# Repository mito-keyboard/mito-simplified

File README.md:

# Mito PCB

The pcb for my [custom keyboard](https://github.com/KOEGlike/mito)

## Sponsor

Much thanks to pcbway for sponsoring this project, the video is in the making, stay tuned! The PCBs and stencil are very high quality!!

## Gallery

## Name

Inspired by the mitosis of cells

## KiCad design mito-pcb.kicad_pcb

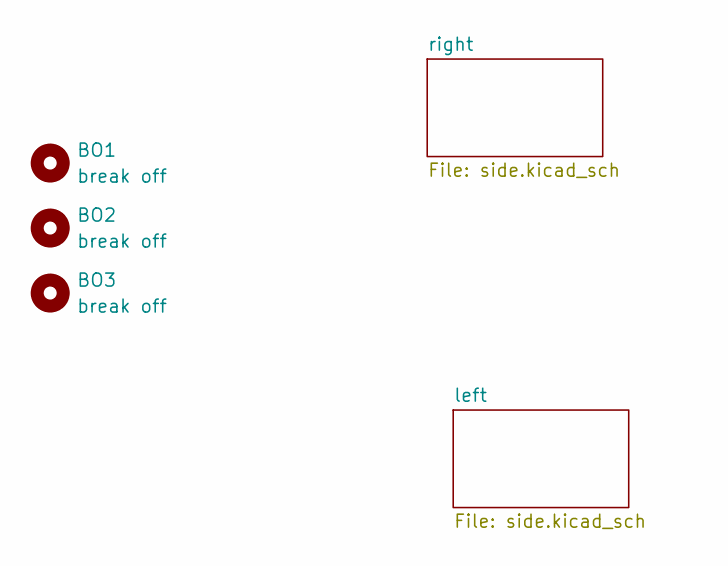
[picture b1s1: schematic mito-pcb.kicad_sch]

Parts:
BO1, BO2, BO3: break off; mouse-bite-2mm-slot

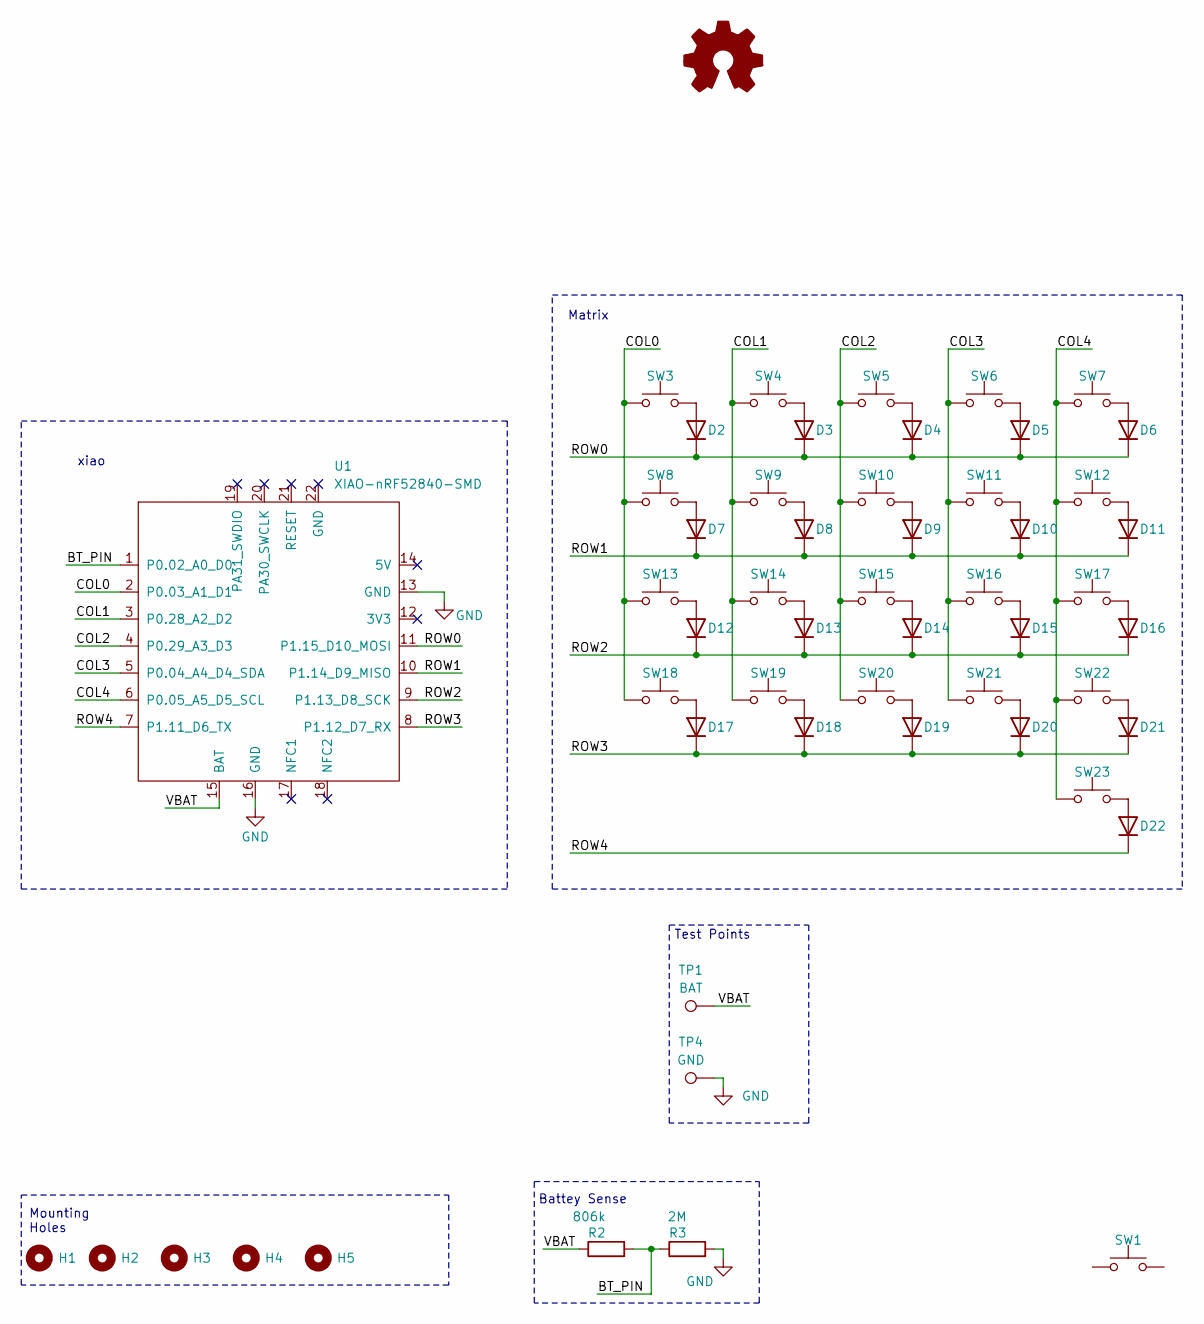
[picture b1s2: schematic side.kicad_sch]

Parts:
D2, D3, D4, D5, D6, D7, D8, D9, D10, D11, D12, D13, D14, D15, D16, D17, D18, D19, D20, D21, D22: 1N5819; D_SOD-123; LCSC C963381
H1, H2, H3, H4, H5: MountingHole; MountingHole_2mm
LOGO1: Logo_Open_Hardware_Small; BM logo
R2: 806k; R_0805_2012Metric; LCSC C3016043
R3: 2M; R_0805_2012Metric; LCSC C11512
SW1, SW3, SW4, SW5, SW6, SW7, SW8, SW9, SW10, SW11, SW12, SW13, SW14, SW15, SW16, SW17, SW18, SW19, SW20, SW21, SW22, SW23: SW_Push; SW_choc_v1_HS_CPG135001S30_1u; LCSC C5333465
TP1: BAT; TestPoint_Pad_D2.0mm
TP4: GND; TestPoint_Pad_D2.0mm
U1: XIAO-nRF52840-SMD; modified-XIAO-nRF52840-SMD

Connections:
/left/BT_PIN: R2.2, R3.1, U1.1 (P0.02_A0_D0)
/left/COL0: SW3.1, SW8.1, SW13.1, SW18.1, U1.2 (P0.03_A1_D1)
/left/COL1: SW4.1, SW9.1, SW14.1, SW19.1, U1.3 (P0.28_A2_D2)
/left/COL2: SW5.1, SW10.1, SW15.1, SW20.1, U1.4 (P0.29_A3_D3)
/left/COL3: SW6.1, SW11.1, SW16.1, SW21.1, U1.5 (P0.04_A4_D4_SDA)
/left/COL4: SW7.1, SW12.1, SW17.1, SW22.1, SW23.1, U1.6 (P0.05_A5_D5_SCL)
/left/ROW0: D2.1 (K), D3.1 (K), D4.1 (K), D5.1 (K), D6.1 (K), U1.11 (P1.15_D10_MOSI)
/left/ROW1: D7.1 (K), D8.1 (K), D9.1 (K), D10.1 (K), D11.1 (K), U1.10 (P1.14_D9_MISO)
/left/ROW2: D12.1 (K), D13.1 (K), D14.1 (K), D15.1 (K), D16.1 (K), U1.9 (P1.13_D8_SCK)
/left/ROW3: D17.1 (K), D18.1 (K), D19.1 (K), D20.1 (K), D21.1 (K), U1.8 (P1.12_D7_RX)
/left/ROW4: D22.1 (K), U1.7 (P1.11_D6_TX)
/left/VBAT: R2.1, TP1.1, U1.15 (BAT)
GND: R3.2, TP4.1, U1.13 (GND), U1.16 (GND); also elsewhere on the board
unnamed: D2.2 (A), SW3.2
unnamed: D3.2 (A), SW4.2
unnamed: D4.2 (A), SW5.2
unnamed: D5.2 (A), SW6.2
unnamed: D6.2 (A), SW7.2
unnamed: D7.2 (A), SW8.2
unnamed: D8.2 (A), SW9.2
unnamed: D9.2 (A), SW10.2
unnamed: D10.2 (A), SW11.2
unnamed: D11.2 (A), SW12.2
unnamed: D12.2 (A), SW13.2
unnamed: D13.2 (A), SW14.2
unnamed: D14.2 (A), SW15.2
unnamed: D15.2 (A), SW16.2
unnamed: D16.2 (A), SW17.2
unnamed: D17.2 (A), SW18.2
unnamed: D18.2 (A), SW19.2
unnamed: D19.2 (A), SW20.2
unnamed: D20.2 (A), SW21.2
unnamed: D21.2 (A), SW22.2
unnamed: D22.2 (A), SW23.2

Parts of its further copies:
D44, D45, D46, D47, D48, D49, D50, D51, D52, D53, D54, D55, D56, D57, D58, D59, D60, D61, D62, D63, D64: 1N5819; D_SOD-123; LCSC C963381
H6, H7, H8, H9, H10: MountingHole; MountingHole_2mm
R9: 806k; R_0805_2012Metric; LCSC C3016043
R10: 2M; R_0805_2012Metric; LCSC C11512
SW26, SW27, SW28, SW29, SW30, SW31, SW32, SW33, SW34, SW35, SW36, SW37, SW38, SW39, SW40, SW41, SW42, SW43, SW44, SW45, SW46: SW_Push; SW_choc_v1_HS_CPG135001S30_1u; LCSC C5333465
TP2: BAT; TestPoint_Pad_D2.0mm
TP8: GND; TestPoint_Pad_D2.0mm
U3: XIAO-nRF52840-SMD; modified-XIAO-nRF52840-SMD

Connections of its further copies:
/right/BT_PIN: R9.2, R10.1, U3.1 (P0.02_A0_D0)
/right/COL0: SW26.1, SW31.1, SW36.1, SW41.1, U3.2 (P0.03_A1_D1)
/right/COL1: SW27.1, SW32.1, SW37.1, SW42.1, U3.3 (P0.28_A2_D2)
/right/COL2: SW28.1, SW33.1, SW38.1, SW43.1, U3.4 (P0.29_A3_D3)
/right/COL3: SW29.1, SW34.1, SW39.1, SW44.1, U3.5 (P0.04_A4_D4_SDA)
/right/COL4: SW30.1, SW35.1, SW40.1, SW45.1, SW46.1, U3.6 (P0.05_A5_D5_SCL)
/right/ROW0: D44.1 (K), D45.1 (K), D46.1 (K), D47.1 (K), D48.1 (K), U3.11 (P1.15_D10_MOSI)
/right/ROW1: D49.1 (K), D50.1 (K), D51.1 (K), D52.1 (K), D53.1 (K), U3.10 (P1.14_D9_MISO)
/right/ROW2: D54.1 (K), D55.1 (K), D56.1 (K), D57.1 (K), D58.1 (K), U3.9 (P1.13_D8_SCK)
/right/ROW3: D59.1 (K), D60.1 (K), D61.1 (K), D62.1 (K), D63.1 (K), U3.8 (P1.12_D7_RX)
/right/ROW4: D64.1 (K), U3.7 (P1.11_D6_TX)
/right/VBAT: R9.1, TP2.1, U3.15 (BAT)
GND: R10.2, TP8.1, U3.13 (GND), U3.16 (GND); also elsewhere on the board
unnamed: D44.2 (A), SW26.2
unnamed: D45.2 (A), SW27.2
unnamed: D46.2 (A), SW28.2
unnamed: D47.2 (A), SW29.2
unnamed: D48.2 (A), SW30.2
unnamed: D49.2 (A), SW31.2
unnamed: D50.2 (A), SW32.2
unnamed: D51.2 (A), SW33.2
unnamed: D52.2 (A), SW34.2
unnamed: D53.2 (A), SW35.2
unnamed: D54.2 (A), SW36.2
unnamed: D55.2 (A), SW37.2
unnamed: D56.2 (A), SW38.2
unnamed: D57.2 (A), SW39.2
unnamed: D58.2 (A), SW40.2
unnamed: D59.2 (A), SW41.2
unnamed: D60.2 (A), SW42.2
unnamed: D61.2 (A), SW43.2
unnamed: D62.2 (A), SW44.2
unnamed: D63.2 (A), SW45.2
unnamed: D64.2 (A), SW46.2

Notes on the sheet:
Battey Sense
Matrix
Mounting Holes
Test Points
xiao

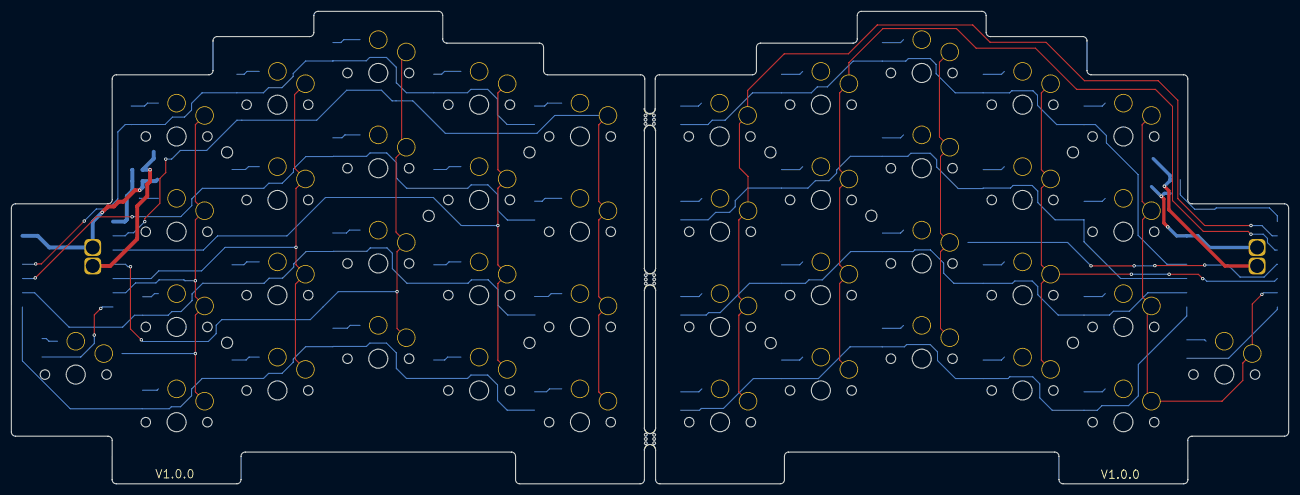
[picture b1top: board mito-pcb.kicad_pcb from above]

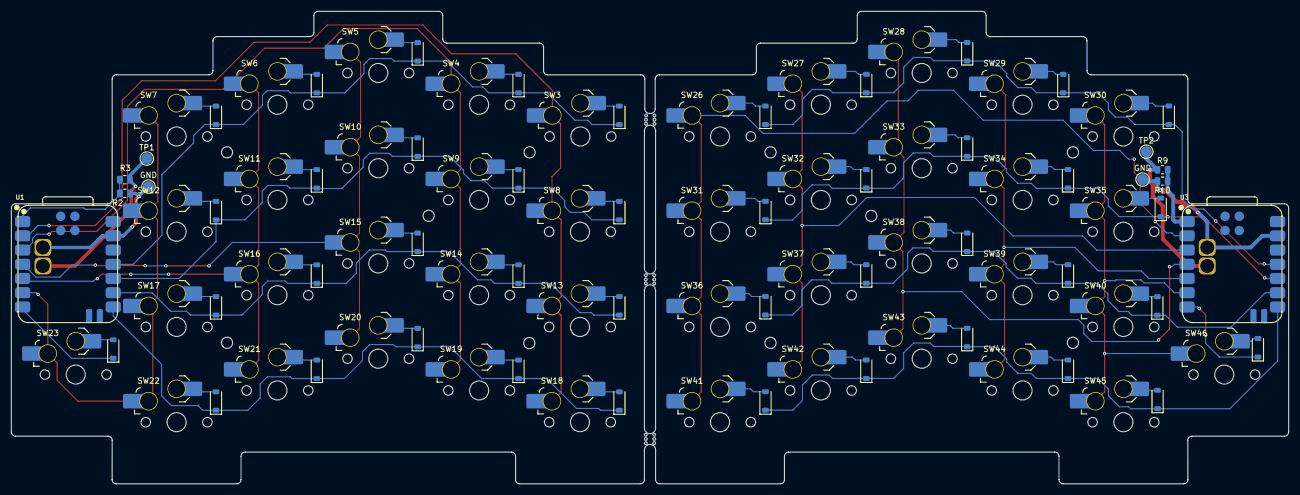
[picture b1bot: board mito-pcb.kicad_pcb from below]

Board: 2 copper layers, 228.0 x 84.3 mm, 107 parts (99 on the bottom side), 67 nets.

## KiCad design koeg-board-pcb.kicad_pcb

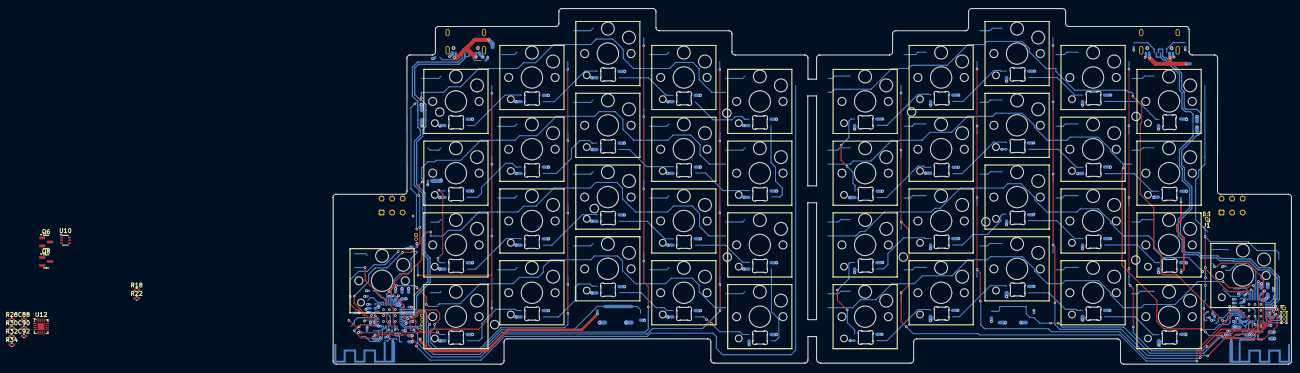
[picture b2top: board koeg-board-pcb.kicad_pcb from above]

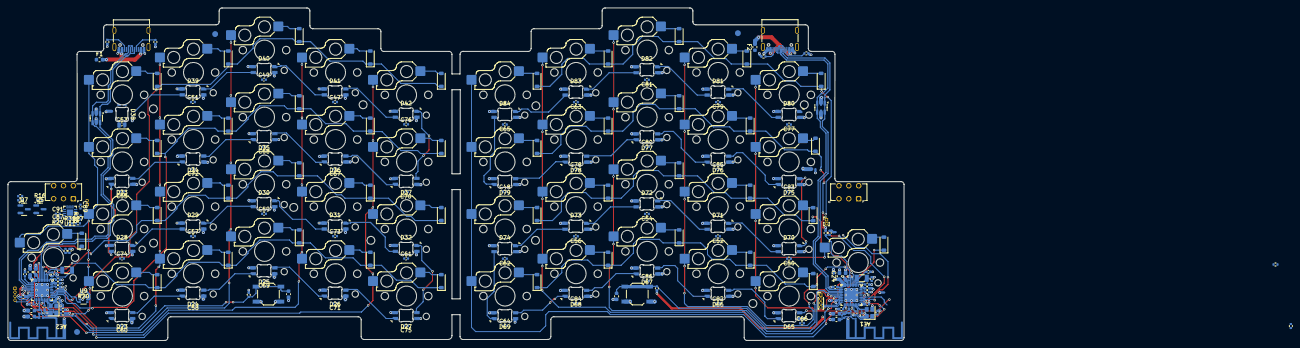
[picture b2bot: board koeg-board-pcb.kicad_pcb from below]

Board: 4 copper layers, 227.1 x 84.3 mm, 277 parts (215 on the bottom side), 173 nets.

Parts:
AE1: PCB_Antenna; flipped_pcb_antenna
AE2: PCB_Antenna; pcb_antenna
C2, C18: 100nF; C_0603_1608Metric
C4, C20, C41, C42, C43, C44, C47, C48, C49, C50, C51, C52, C53, C54, C55, C56, C57, C58, C59, C60, C61, C62, C63, C64, C65, C66, C67, C68, C69, C70, C71, C72, C73, C74, C75, C76, C77, C78, C79, C80, C81, C82, C83, C84, C85, C86: 100nF; C_0402_1005Metric
C5, C21: 100pF; C_0402_1005Metric
C6, C22: 820pF; C_0402_1005Metric
C7, C23, C39, C40: 1uF; C_0402_1005Metric
C9, C25, C87, C88, C89, C90, C91, C92: 4.7uF; C_0402_1005Metric
C10, C19, C24, C26: 4.7uF; C_0603_1608Metric
C11, C12, C15, C16, C27, C28, C31, C32: 12pF; C_0402_1005Metric
C13, C29: 1pF; C_0603_1608Metric
C14, C30: 1.2pF; C_0603_1608Metric
D2, D3, D4, D5, D6, D7, D8, D9, D10, D11, D12, D13, D14, D15, D16, D17, D18, D19, D20, D21, D22, D44, D45, D46, D47, D48, D49, D50, D51, D52, D53, D54, D55, D56, D57, D58, D59, D60, D61, D62, D63, D64: 1N5819; D_SOD-123
D23, D24, D25, D26, D27, D28, D29, D30, D31, D32, D33, D34, D35, D36, D37, D38, D39, D40, D41, D42, D65, D66, D67, D68, D69, D70, D71, D72, D73, D74, D75, D76, D77, D78, D79, D80, D81, D82, D83, D84: SK6812MINI-E; LED_6028R
F1, F2: 500mA; Fuse_0603_1608Metric
FID1, FID2, FID3: Fiducial; Fiducial_1.5mm_Mask3mm
H1, H2, H3, H4, H5, H6, H7, H8, H9, H10: MountingHole; MountingHole_2mm
J1, J4: Conn_01x02; PinHeader_1x02_P1.00mm_Vertical
J2, J5: SWD_Connector; PinHeader_1x04_P1.00mm_Vertical
J3, J6: USB_C_Receptacle_USB2.0_16P; USB_C_Receptacle_G-Switch_GT-USB-7010ASV
L4, L9: 4.7nH; L_0402_1005Metric
L5, L10: 2.2nH; L_0402_1005Metric
Q5, Q6: AO3401A; SOT-23
Q7, Q8: 2N7002; SOT-23
R1, R8: 100K; R_0402_1005Metric
R2, R9: 806k; R_0402_1005Metric
R3, R10: 2M; R_0402_1005Metric
R4, R5, R11, R12: 5.1k; R_0402_1005Metric
R6, R7: 100R; R_0402_1005Metric
R13, R14, R16, R18, R20, R22: 10k; R_0402_1005Metric
R27, R28: 3.9k; R_0402_1005Metric
R29, R30, R31, R32, R33, R34: 1.5k; R_0402_1005Metric
SW1, SW24: Reset Button; SW_SPST_TL3342
SW2, SW25: SW_On_Off; SW_CK_JS202011AQN_DPDT_Angled
SW3, SW4, SW5, SW6, SW7, SW8, SW9, SW10, SW11, SW12, SW13, SW14, SW15, SW16, SW17, SW18, SW19, SW20, SW21, SW22, SW26, SW27, SW28, SW29, SW30, SW31, SW32, SW33, SW34, SW35, SW36, SW37, SW38, SW39, SW40, SW41, SW42, SW43, SW44, SW45: SW_Push; SW_Hotswap_Kailh_Choc_V1V2_1.00u
SW23, SW46: SW_Push; SW_Hotswap_Kailh_Choc_V1V2_1.75u_90deg
U2, U5: USBLC6-2SC6; SOT-23-6
U7, U8: nRF52833_QDxx; QFN-40-1EP_5x5mm_P0.4mm_EP3.6x3.6mm
U9, U10: TXB0101DCK; SOT-363_SC-70-6
U11, U12: BQ24075RGT; VQFN-16-1EP_3x3mm_P0.5mm_EP1.6x1.6mm
Y1, Y2: 32MHz; Crystal_SMD_2520-4Pin_2.5x2.0mm
Y3, Y4: 32.768 kHz; Crystal_SMD_3215-2Pin_3.2x1.5mm

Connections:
/left/ANT: AE2.2 (PCB_Trace), C13.2, L4.1, L5.2, U7.24 (ANT)
/left/BT_PIN: R2.2, R3.1, U7.6 (P1.09)
/left/CC1: J3.A5 (CC1), R4.1
/left/CC2: J3.B5 (CC2), R5.1
/left/COL0: SW3.2, SW8.2, SW13.2, SW18.2, U7.34 (AIN5/P0.29)
/left/COL1: SW4.2, SW9.2, SW14.2, SW19.2, U7.7 (P0.11)
/left/COL2: SW5.2, SW10.2, SW15.2, SW20.2, U7.14 (P0.15)
/left/COL3: SW6.2, SW11.2, SW16.2, SW21.2, U7.15 (P0.17)
/left/COL4: SW7.2, SW12.2, SW17.2, SW22.2, SW23.2, U7.17 (P0.20)
/left/DEC1: C4.1, U7.1 (DEC1)
/left/DEC3: C5.1, U7.27 (DEC3)
/left/DEC4-6: C7.1, U7.26 (DEC6), U7.38 (DEC4)
/left/DEC5: C6.1, U7.21 (DEC5)
/left/DECUSB: C9.1, U7.11 (DECUSB)
/left/LED_EN: R6.1, U7.35 (AIN6/P0.30)
/left/LED_PIN: U7.33 (AIN4/P0.28), U9.3 (A)
/left/RESET: C2.2, R1.2, SW1.1, U7.16 (P0.18/~RESET)
/left/ROW0: D2.1 (K), D3.1 (K), D4.1 (K), D5.1 (K), D6.1 (K), U7.32 (AIN0/P0.02)
/left/ROW1: D7.1 (K), D8.1 (K), D9.1 (K), D10.1 (K), D11.1 (K), U7.31 (AIN1/P0.03)
/left/ROW2: D12.1 (K), D13.1 (K), D14.1 (K), D15.1 (K), D16.1 (K), U7.4 (AIN2/P0.04)
/left/ROW3: D17.1 (K), D18.1 (K), D19.1 (K), D20.1 (K), D21.1 (K), U7.5 (AIN3/P0.05)
/left/ROW4: D22.1 (K), U7.22 (NFC1/P0.09)
/left/SWDCLK: J2.4, U7.20 (SWDCLK)
/left/SWDIO: J2.3, U7.19 (SWDIO)
/left/USB_D+: J3.A6 (D+), J3.B6 (D+), U2.3 (I/O2), U2.4 (I/O2), U7.13 (D+)
/left/USB_D-: J3.A7 (D-), J3.B7 (D-), U2.1 (I/O1), U2.6 (I/O1), U7.12 (D-)
/left/VBAT: C89.2, J1.1, R2.1, U11.2 (BAT), U11.3 (BAT)
/left/VBUS: C87.2, F1.1, U2.5 (VBUS), U11.13 (IN)
/left/VSW: C19.1, Q5.3 (D), R16.2, SW2.2 (B), U7.9 (VDDH), U7.10 (VBUS), U9.6 (V_{CCB}), U11.6 (EN1)
/left/V_SYS: C10.2, C39.2, C41.2, C43.2, J2.2, R1.1, R20.2, U7.8 (VDD), U7.18 (VDD), U7.30 (VDD), U7.40 (VDD), U9.1 (V_{CCA})
/left/XC1: C11.1, U7.28 (XC1), Y1.1
/left/XC2: C12.1, U7.29 (XC2), Y1.3
/left/XL1: C31.2, U7.2 (XL1/P0.00), Y3.2
/left/XL2: C15.2, U7.3 (XL2/P0.01), Y3.1
/left/leds/DATA: D23.3 (DIN), U9.4 (B)
/left/leds/LED_PWR: C47.2, C49.2, C51.2, C53.2, C55.2, C57.2, C58.2, C59.2, C60.2, C61.2, C67.2, C68.2, C69.2, C70.2, C71.2, C72.2, C73.2, C74.2, C75.2, C76.2, D23.1 (VDD), D24.1 (VDD), D25.1 (VDD), D26.1 (VDD), D27.1 (VDD), D28.1 (VDD), D29.1 (VDD), D30.1 (VDD), D31.1 (VDD), D32.1 (VDD), D33.1 (VDD), D34.1 (VDD), D35.1 (VDD), D36.1 (VDD), D37.1 (VDD), D38.1 (VDD), D39.1 (VDD), D40.1 (VDD), D41.1 (VDD), D42.1 (VDD), Q5.2 (S)
/left/power/ILIM: R29.1, U11.12 (ILIM)
/left/power/ISET: R27.1, U11.16 (ISET)
/left/power/REG-OUT: C91.2, SW2.1 (A), U11.10 (OUT), U11.11 (OUT)
/left/power/TMR: R31.1, U11.14 (TMR)
/left/power/TS: R33.2, U11.1 (TS)
/right/ANT: AE1.2 (PCB_Trace), C29.2, L9.1, L10.2, U8.24 (ANT)
/right/BT_PIN: R9.2, R10.1, U8.6 (P1.09)
/right/CC1: J6.A5 (CC1), R11.1
/right/CC2: J6.B5 (CC2), R12.1
/right/COL0: SW26.2, SW31.2, SW36.2, SW41.2, U8.34 (AIN5/P0.29)
/right/COL1: SW27.2, SW32.2, SW37.2, SW42.2, U8.7 (P0.11)
/right/COL2: SW28.2, SW33.2, SW38.2, SW43.2, U8.14 (P0.15)
/right/COL3: SW29.2, SW34.2, SW39.2, SW44.2, U8.15 (P0.17)
/right/COL4: SW30.2, SW35.2, SW40.2, SW45.2, SW46.2, U8.17 (P0.20)
/right/DEC1: C20.1, U8.1 (DEC1)
/right/DEC3: C21.1, U8.27 (DEC3)
/right/DEC4-6: C23.1, U8.26 (DEC6), U8.38 (DEC4)
/right/DEC5: C22.1, U8.21 (DEC5)
/right/DECUSB: C25.1, U8.11 (DECUSB)
/right/LED_EN: R7.1, U8.35 (AIN6/P0.30)
/right/LED_PIN: U8.33 (AIN4/P0.28), U10.3 (A)
/right/RESET: C18.2, R8.2, SW24.1, U8.16 (P0.18/~RESET)
/right/ROW0: D44.1 (K), D45.1 (K), D46.1 (K), D47.1 (K), D48.1 (K), U8.32 (AIN0/P0.02)
/right/ROW1: D49.1 (K), D50.1 (K), D51.1 (K), D52.1 (K), D53.1 (K), U8.31 (AIN1/P0.03)
/right/ROW2: D54.1 (K), D55.1 (K), D56.1 (K), D57.1 (K), D58.1 (K), U8.4 (AIN2/P0.04)
/right/ROW3: D59.1 (K), D60.1 (K), D61.1 (K), D62.1 (K), D63.1 (K), U8.5 (AIN3/P0.05)
/right/ROW4: D64.1 (K), U8.22 (NFC1/P0.09)
/right/SWDCLK: J5.4, U8.20 (SWDCLK)
/right/SWDIO: J5.3, U8.19 (SWDIO)
/right/USB_D+: J6.A6 (D+), J6.B6 (D+), U5.3 (I/O2), U5.4 (I/O2), U8.13 (D+)
/right/USB_D-: J6.A7 (D-), J6.B7 (D-), U5.1 (I/O1), U5.6 (I/O1), U8.12 (D-)
/right/VBAT: C90.2, J4.1, R9.1, U12.2 (BAT), U12.3 (BAT)
/right/VBUS: C88.2, F2.1, U5.5 (VBUS), U12.13 (IN)
/right/VSW: C24.1, Q6.3 (D), R18.2, SW25.2 (B), U8.9 (VDDH), U8.10 (VBUS), U10.6 (V_{CCB}), U12.6 (EN1)
/right/V_SYS: C26.2, C40.2, C42.2, C44.2, J5.2, R8.1, R22.2, U8.8 (VDD), U8.18 (VDD), U8.30 (VDD), U8.40 (VDD), U10.1 (V_{CCA})
/right/XC1: C27.1, U8.28 (XC1), Y2.1
/right/XC2: C28.1, U8.29 (XC2), Y2.3
/right/XL1: C32.2, U8.2 (XL1/P0.00), Y4.2
/right/XL2: C16.2, U8.3 (XL2/P0.01), Y4.1
/right/leds/DATA: D65.3 (DIN), U10.4 (B)
/right/leds/LED_PWR: C48.2, C50.2, C52.2, C54.2, C56.2, C62.2, C63.2, C64.2, C65.2, C66.2, C77.2, C78.2, C79.2, C80.2, C81.2, C82.2, C83.2, C84.2, C85.2, C86.2, D65.1 (VDD), D66.1 (VDD), D67.1 (VDD), D68.1 (VDD), D69.1 (VDD), D70.1 (VDD), D71.1 (VDD), D72.1 (VDD), D73.1 (VDD), D74.1 (VDD), D75.1 (VDD), D76.1 (VDD), D77.1 (VDD), D78.1 (VDD), D79.1 (VDD), D80.1 (VDD), D81.1 (VDD), D82.1 (VDD), D83.1 (VDD), D84.1 (VDD), Q6.2 (S)
/right/power/ILIM: R30.1, U12.12 (ILIM)
/right/power/ISET: R28.1, U12.16 (ISET)
/right/power/REG-OUT: C92.2, SW25.1 (A), U12.10 (OUT), U12.11 (OUT)
/right/power/TMR: R32.1, U12.14 (TMR)
/right/power/TS: R34.2, U12.1 (TS)
GND: AE1.1 (FEED), AE2.1 (FEED), C2.1, C4.2, C5.2, C6.2, C7.2, C9.2, C10.1, C11.2, C12.2, C13.1, C14.2, C15.1, C16.1, C18.1, C19.2, C20.2, C21.2, C22.2, C23.2, C24.2, C25.2, C26.1, C27.2, C28.2, C29.1, C30.2, C31.1, C32.1, C39.1, C40.1, C41.1, C42.1, C43.1, C44.1, C47.1, C48.1, C49.1, C50.1, C51.1, C52.1, C53.1, C54.1, C55.1, C56.1, C57.1, C58.1, C59.1, C60.1, C61.1, C62.1, C63.1, C64.1, C65.1, C66.1, C67.1, C68.1, C69.1, C70.1, C71.1, C72.1, C73.1, C74.1, C75.1, C76.1, C77.1, C78.1, C79.1, C80.1, C81.1, C82.1, C83.1, C84.1, C85.1, C86.1, C87.1, C88.1, C89.1, C90.1, C91.1, C92.1, D23.4 (VSS), D24.4 (VSS), D25.4 (VSS), D26.4 (VSS), D27.4 (VSS), D28.4 (VSS), D29.4 (VSS), D30.4 (VSS), D31.4 (VSS), D32.4 (VSS), D33.4 (VSS), D34.4 (VSS), D35.4 (VSS), D36.4 (VSS), D37.4 (VSS), D38.4 (VSS), D39.4 (VSS), D40.4 (VSS), D41.4 (VSS), D42.4 (VSS), D65.4 (VSS), D66.4 (VSS), D67.4 (VSS), D68.4 (VSS), D69.4 (VSS), D70.4 (VSS), D71.4 (VSS), D72.4 (VSS), D73.4 (VSS), D74.4 (VSS), D75.4 (VSS), D76.4 (VSS), D77.4 (VSS), D78.4 (VSS), D79.4 (VSS), D80.4 (VSS), D81.4 (VSS), D82.4 (VSS), D83.4 (VSS), D84.4 (VSS), J1.2, J2.1, J3.A1 (GND), J3.A12 (GND), J3.B1 (GND), J3.B12 (GND), J4.2, J5.1, J6.A1 (GND), J6.A12 (GND), J6.B1 (GND), J6.B12 (GND), Q7.2 (S), Q8.2 (S), R3.2, R4.2, R5.2, R10.2, R11.2, R12.2, R13.1, R14.1, R27.2, R28.2, R29.2, R30.2, R31.2, R32.2, R33.1, R34.1, SW1.2, SW24.2, U2.2 (GND), U5.2 (GND), U7.25 (VSS_PA), U7.37 (VSS), U7.41 (VSS), U8.25 (VSS_PA), U8.37 (VSS), U8.41 (VSS), U9.2 (GND), U10.2 (GND), U11.4 (~CE), U11.5 (EN2), U11.8 (VSS), U11.15 (SYSOFF), U11.17 (VSS), U12.4 (~CE), U12.5 (EN2), U12.8 (VSS), U12.15 (SYSOFF), U12.17 (VSS), Y1.2, Y1.4, Y2.2, Y2.4
unnamed: C14.1, L4.2, L5.1
unnamed: C30.1, L9.2, L10.1
unnamed: D2.2 (A), SW3.1
unnamed: D3.2 (A), SW4.1
unnamed: D4.2 (A), SW5.1
unnamed: D5.2 (A), SW6.1
unnamed: D6.2 (A), SW7.1
unnamed: D7.2 (A), SW8.1
unnamed: D8.2 (A), SW9.1
unnamed: D9.2 (A), SW10.1
unnamed: D10.2 (A), SW11.1
unnamed: D11.2 (A), SW12.1
unnamed: D12.2 (A), SW13.1
unnamed: D13.2 (A), SW14.1
unnamed: D14.2 (A), SW15.1
unnamed: D15.2 (A), SW16.1
unnamed: D16.2 (A), SW17.1
unnamed: D17.2 (A), SW18.1
unnamed: D18.2 (A), SW19.1
unnamed: D19.2 (A), SW20.1
unnamed: D20.2 (A), SW21.1
unnamed: D21.2 (A), SW22.1
unnamed: D22.2 (A), SW23.1
unnamed: D23.2 (DOUT), D24.3 (DIN)
unnamed: D24.2 (DOUT), D25.3 (DIN)
unnamed: D25.2 (DOUT), D26.3 (DIN)
unnamed: D26.2 (DOUT), D27.3 (DIN)
unnamed: D27.2 (DOUT), D32.3 (DIN)
unnamed: D28.3 (DIN), D29.2 (DOUT)
unnamed: D28.2 (DOUT), D33.3 (DIN)
unnamed: D29.3 (DIN), D30.2 (DOUT)
unnamed: D30.3 (DIN), D31.2 (DOUT)
unnamed: D31.3 (DIN), D32.2 (DOUT)
unnamed: D33.2 (DOUT), D34.3 (DIN)
unnamed: D34.2 (DOUT), D35.3 (DIN)
unnamed: D35.2 (DOUT), D36.3 (DIN)
unnamed: D36.2 (DOUT), D37.3 (DIN)
unnamed: D37.2 (DOUT), D42.3 (DIN)
unnamed: D38.3 (DIN), D39.2 (DOUT)
unnamed: D39.3 (DIN), D40.2 (DOUT)
unnamed: D40.3 (DIN), D41.2 (DOUT)
unnamed: D41.3 (DIN), D42.2 (DOUT)
unnamed: D44.2 (A), SW26.1
unnamed: D45.2 (A), SW27.1
unnamed: D46.2 (A), SW28.1
unnamed: D47.2 (A), SW29.1
unnamed: D48.2 (A), SW30.1
unnamed: D49.2 (A), SW31.1
unnamed: D50.2 (A), SW32.1
unnamed: D51.2 (A), SW33.1
unnamed: D52.2 (A), SW34.1
unnamed: D53.2 (A), SW35.1
unnamed: D54.2 (A), SW36.1
unnamed: D55.2 (A), SW37.1
unnamed: D56.2 (A), SW38.1
unnamed: D57.2 (A), SW39.1
unnamed: D58.2 (A), SW40.1
unnamed: D59.2 (A), SW41.1
unnamed: D60.2 (A), SW42.1
unnamed: D61.2 (A), SW43.1
unnamed: D62.2 (A), SW44.1
unnamed: D63.2 (A), SW45.1
unnamed: D64.2 (A), SW46.1
unnamed: D65.2 (DOUT), D66.3 (DIN)
unnamed: D66.2 (DOUT), D67.3 (DIN)
unnamed: D67.2 (DOUT), D68.3 (DIN)
unnamed: D68.2 (DOUT), D69.3 (DIN)
unnamed: D69.2 (DOUT), D74.3 (DIN)
unnamed: D70.3 (DIN), D71.2 (DOUT)
unnamed: D70.2 (DOUT), D75.3 (DIN)
unnamed: D71.3 (DIN), D72.2 (DOUT)
unnamed: D72.3 (DIN), D73.2 (DOUT)
unnamed: D73.3 (DIN), D74.2 (DOUT)
unnamed: D75.2 (DOUT), D76.3 (DIN)
unnamed: D76.2 (DOUT), D77.3 (DIN)
unnamed: D77.2 (DOUT), D78.3 (DIN)
unnamed: D78.2 (DOUT), D79.3 (DIN)
unnamed: D79.2 (DOUT), D84.3 (DIN)
unnamed: D80.3 (DIN), D81.2 (DOUT)
unnamed: D81.3 (DIN), D82.2 (DOUT)
unnamed: D82.3 (DIN), D83.2 (DOUT)
unnamed: D83.3 (DIN), D84.2 (DOUT)
unnamed: F1.2, J3.A4 (VBUS), J3.A9 (VBUS), J3.B4 (VBUS), J3.B9 (VBUS)
unnamed: F2.2, J6.A4 (VBUS), J6.A9 (VBUS), J6.B4 (VBUS), J6.B9 (VBUS)
unnamed: Q5.1 (G), Q7.3 (D), R16.1
unnamed: Q6.1 (G), Q8.3 (D), R18.1
unnamed: Q7.1 (G), R6.2, R13.2
unnamed: Q8.1 (G), R7.2, R14.2
unnamed: R20.1, U9.5 (OE)
unnamed: R22.1, U10.5 (OE)

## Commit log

2024-10-29 before auto route
2024-10-29 autorouted
2024-10-30 one side done
2024-10-31 reassigned basic components, now comes the leds
2024-10-31 placed leds
2024-10-31 routed left side
2024-11-02 placed right side
2024-11-02 routed right side, added filets
2024-11-02 added propper brake offs
2024-11-02 idk what changed here
2024-11-02 added fillzone
2024-11-02 exported 3e model
2024-11-04 wired up the new votlage converter, removed small smd componenets
2024-11-09 placed components
2024-11-10 the right side still needs to be routed
2024-11-10 chaned usb c footprint, flipped fiducials
2024-11-18 adding power and battery management
2024-11-24 finished power circuit
2024-11-24 added submodule instead of code for footprint library
2024-11-24 made schemtic look better
2024-11-26 switched oout led footprint
2024-11-26 next revisioncomplete
2024-11-26 reassigned refrences
2024-11-26 updated some things
2024-11-26 removed unused via pads
2024-11-26 added mousebites properly this time
2024-11-27 updated fill zones
2024-11-27 idk what i chaned
2024-11-28 switched to chip antenna
2024-11-29 added lcsc part numbers
2024-11-30 idk what changed
2024-11-30 fixed minor things
2024-12-01 added test points
2024-12-01 removed unnecessary vias next to the led decoupling caps
2024-12-01 fixed fillzones
2024-12-01 fixed fillzones, forgor to save last time
2024-12-02 upated routing of colums
2024-12-03 cleand up things
2024-12-03 removed silkscreen idenrifiers
2024-12-06 added logo, cleaned up traces
2024-12-06 added pattern
2024-12-06 Revert "added pattern"
    This reverts commit fcd4d5045a61e5ad3fdb50feb400667130e6be26.
2024-12-06 checked schematic again, fixed bugs
2024-12-13 removed prod folder, added version silkscreen, incrase no ground plane are around antenna
2024-12-13 removed junk
2024-12-13 clean up
2024-12-13 rename
2024-12-13 0.09 mm to 0.1 mm clearnce pt.1
2024-12-13 pt2 of 0.09mm to 0.1mm
2024-12-13 pt3 of 0.09mm to 0.1mm clearace
2024-12-14 hmmmm
2024-12-14 fixed edge cuts, switched to marbastlib switches
2024-12-14 fixed edge cuts more
2024-12-14 found more edge cute issues💀
2024-12-15 more edgecuts aaaaaagghhh
2024-12-15 refilled zones
2024-12-27 uuid changes for exporting with jlcfab plugin
2025-01-02 added missing 3d models
    i couldn't find the 3d model for the usb c port, so i used a similar one, the only problem is that the feet aren't in the same place as on the footprint, so it clips into the board
2025-01-05 removed text markings
2025-01-10 moved 9.0(nightly)
2025-01-19 removed rescue layers
2025-01-29 made a nice readme
2025-01-29 made it more beautfullsfsadfdsafsdf
2025-02-01 new kicad version, added lcsc for the on/of switch
2025-02-09 veriosn bump
2025-03-08 kicad did something
2025-03-22 fixed wrong resistor value for power management chip
2025-09-17 made progress, added xiao libray, removed almost all of the old schmeatic, started ot edit pcb
2025-09-17 changed xioa footprint, edited edge cuts, layed out
2025-09-18 routed left half
2025-09-18 renamed the custom footprint
2025-09-18 worked on guide
2025-09-19 Refactor code structure for improved readability and maintainability
2025-09-19 finished guide
2025-10-04 removed not needed fiels
2025-10-04 routed other half,added models
